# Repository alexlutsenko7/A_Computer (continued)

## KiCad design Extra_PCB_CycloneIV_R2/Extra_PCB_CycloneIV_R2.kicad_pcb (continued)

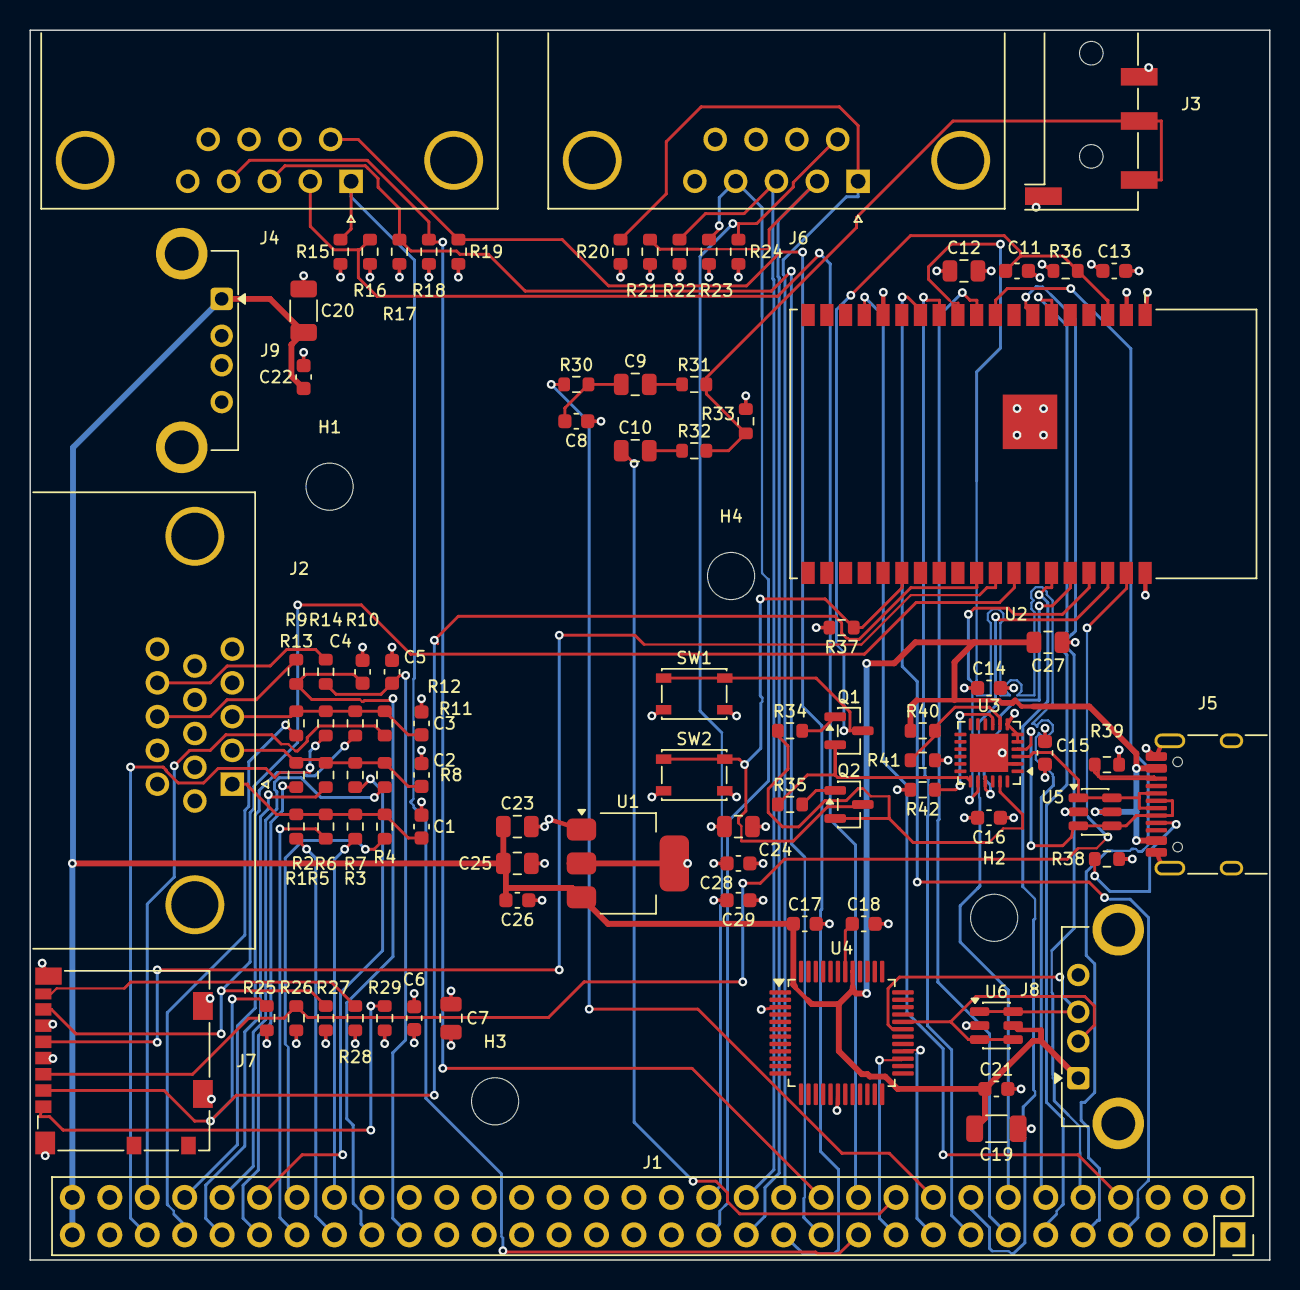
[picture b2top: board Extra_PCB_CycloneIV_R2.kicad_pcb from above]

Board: 4 copper layers, 84.1 x 83.4 mm, 94 parts (0 on the bottom side), 73 nets.

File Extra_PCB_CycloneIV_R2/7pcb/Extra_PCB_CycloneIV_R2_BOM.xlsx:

Item | Qty | Designator | Value | Description | Manufacturer | Manufacturer Part # | Footprint | Mount | LCSC Part #
1 | 5 | C1, C2, C3, C4, C5 | 6p8 | Capacitor 6.8 pF C0G / NP0 0603, 50 V | any |  | C_0603_1608Metric | SMD | C318672
2 | 11 | C6, C8, C13, C15, C16, C17, C21, C22, C26, C28, C29 | 0.1u | Capacitor 100 nF X7R 0603, 16 V or more | any |  | C_0603_1608Metric | SMD | C14663
3 | 7 | C7, C9, C10, C23, C24, C25, C27 | 10u | Capacitor 10 uF X5R 0805, 25 V | Samsung | CL21A106KAYNNNE | C_0805_2012Metric | SMD | C15850
4 | 2 | C11, C14 | 1u | Capacitor 1 uF X5R 0603, 50 V | Samsung | CL10A105KB8NNNC | C_0603_1608Metric | SMD | C15849
5 | 1 | C12 | 22u | Capacitor 22 uF X5R 0805, 25 V | Samsung | CL21A226MAQNNNE | C_0805_2012Metric | SMD | C45783
6 | 1 | C18 | 4.7u | Capacitor 4.7 uF X5R 0603, 16 V | Samsung | CL10A475KO8NNNC | C_0603_1608Metric | SMD | C19666
7 | 2 | C19, C20 | 100u | Capacitor 100 uF X5R 1206, 6.3 V | Samsung | CL31A107MQHNNNE | C_1206_3216Metric | SMD | C15008
8 | 1 | J2 | VGA | D-sub HD 15 socket (VGA), right angle, through hole | CONNFLY | DS1038 series | DSUB-15-HD_Socket_Horizontal_P2.29x2.54mm_CONNFLY_DS1038 | THT | C75754
9 | 1 | J3 | Audio out | 3.5 mm audio jack, 4 pole, SMD | Korean Hroparts | PJ-320D-4A | Jack_3.5mm_KoreanHropartsElec_PJ-320D-4A_Horizontal | SMD | C95562
10 | 2 | J4, J6 | Joystick 2 / Joystick 1 | D-sub 9 plug (pins), right angle, through hole | CONNFLY | DS1037 series | DSUB-9_Pins_Horizontal_P2.77x2.84mm_EdgePinOffset7.70mm_Housed_MountingHolesOff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 | THT | C75750
11 | 1 | J5 | USB-C 5V / console | USB Type-C receptacle, 16 pin, SMD | Korean Hroparts | TYPE-C-31-M-12 | USB_C_Receptacle_HRO_TYPE-C-31-M-12 | SMD | C165948
12 | 1 | J7 | microSD | microSD card socket, push-push | Molex | 104031-0811 | microSD_HC_Molex_104031-0811 | SMD | C585350
13 | 2 | J8, J9 | USB 5V (HDMI dongle) / USB keyboard | USB Type-A receptacle, right angle, through hole | CONNFLY | DS1095-WNR0 | USB_A_Connfly_DS1095 | THT | C19944603
14 | 2 | Q1, Q2 | MMBT3904 | NPN transistor SOT-23 | JSCJ (or any) | MMBT3904 | SOT-23 | SMD | C20526
15 | 3 | R1, R5, R9 | 523 | Resistor 523 R 1 % 0603 | any |  | R_0603_1608Metric | SMD | C23199
16 | 3 | R2, R6, R10 | 1.05k | Resistor 1.05 k 1 % 0603 | any |  | R_0603_1608Metric | SMD | C22832
17 | 3 | R3, R7, R11 | 2.1k | Resistor 2.1 k 1 % 0603 | any |  | R_0603_1608Metric | SMD | C22902
18 | 3 | R4, R8, R12 | 4.22k | Resistor 4.22 k 1 % 0603 | any |  | R_0603_1608Metric | SMD | C23042
19 | 2 | R13, R14 | 22 | Resistor 22 R 1 % 0603 | any |  | R_0603_1608Metric | SMD | C23345
20 | 10 | R15, R16, R17, R18, R19, R20, R21, R22, R23, R24 | 3k3 | Resistor 3.3 k 1 % 0603 | any |  | R_0603_1608Metric | SMD | C22978
21 | 9 | R25, R26, R27, R28, R29, R34, R35, R36, R37 | 10k | Resistor 10 k 1 % 0603 | any |  | R_0603_1608Metric | SMD | C25804
22 | 1 | R30 | 68 | Resistor 68 R 1 % 0603 | any |  | R_0603_1608Metric | SMD | C27592
23 | 2 | R31, R32 | 2.2k | Resistor 2.2 k 1 % 0603 | any |  | R_0603_1608Metric | SMD | C4190
24 | 2 | R33, R42 | 1k | Resistor 1 k 1 % 0603 | any |  | R_0603_1608Metric | SMD | C21190
25 | 2 | R38, R39 | 5.1k | Resistor 5.1 k 1 % 0603 | UNI-ROYAL (or any) | 0603WAF5101T5E | R_0603_1608Metric | SMD | C23186
26 | 1 | R40 | 22k | Resistor 22 k 1 % 0603 | UNI-ROYAL (or any) | 0603WAF2202T5E | R_0603_1608Metric | SMD | C31850
27 | 1 | R41 | 47.5k | Resistor 47.5 k 1 % 0603 | any |  | R_0603_1608Metric | SMD | C23061
28 | 2 | SW1, SW2 | BOOT / EN | Tactile switch SMD | C&K | PTS810 series | SW_SPST_PTS810 | SMD | C116501
29 | 1 | U1 | LDL1117S33R | LDO regulator 3.3 V 1.2 A, SOT-223 | STMicroelectronics | LDL1117S33R | SOT-223-3_TabPin2 | SMD | C435835
30 | 1 | U2 | ESP32-WROVER-E-N16R8 | Wi-Fi / Bluetooth module, 16 MB flash, 8 MB PSRAM | Espressif | ESP32-WROVER-E-N16R8 | ESP32-WROVER-E | SMD | C529589
31 | 1 | U3 | CP2102N-A02-GQFN24 | USB to UART bridge, QFN-24 | Silicon Labs | CP2102N-A02-GQFN24 | QFN-24-1EP_4x4mm_P0.5mm_EP2.6x2.6mm | SMD | C969151
32 | 1 | U4 | CH9350L | USB keyboard / mouse to UART, LQFP-48 | WCH | CH9350L | LQFP-48_7x7mm_P0.5mm | SMD | C109472
33 | 2 | U5, U6 | USBLC6-2SC6 | USB ESD protection, SOT-23-6 | STMicroelectronics | USBLC6-2SC6 | SOT-23-6 | SMD | C7519

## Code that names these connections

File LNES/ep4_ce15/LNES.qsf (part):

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
# Extra_PCB_CycloneIV I/O board: its J1 is wired to U8 with each pin pair swapped
# (J1 pin 2k-1 -> U8 pin 2k, J1 pin 2k -> U8 pin 2k-1). Comment: I/O board J1 pin / U8 pin.
set_location_assignment PIN_AB13 -to ESP_SCK        # J1.7 / U8.8
set_location_assignment PIN_AA13 -to ESP_MOSI       # J1.8 / U8.7
set_location_assignment PIN_AB14 -to ESP_CS_N       # J1.9 / U8.10
set_location_assignment PIN_AA14 -to ESP_MISO       # J1.10 / U8.9
set_location_assignment PIN_AB15 -to ESP_IRQ        # J1.11 / U8.12
set_location_assignment PIN_AA15 -to BT_BCLK        # J1.12 / U8.11
set_location_assignment PIN_AB16 -to BT_LRCK        # J1.13 / U8.14
set_location_assignment PIN_AA16 -to BT_DATA        # J1.14 / U8.13
set_location_assignment PIN_AB17 -to BT_TX          # J1.15 / U8.16
set_location_assignment PIN_AA17 -to BT_RX          # J1.16 / U8.15
set_location_assignment PIN_AB18 -to KB_IN          # J1.17 / U8.18
set_location_assignment PIN_AA18 -to AUDIO_AY       # J1.18 / U8.17
set_location_assignment PIN_AB19 -to KB_OUT         # J1.19 / U8.20
set_location_assignment PIN_AA19 -to AUDIO_BEEP     # J1.20 / U8.19
set_location_assignment PIN_AB20 -to JOY1_UP_N      # J1.21 / U8.22
set_location_assignment PIN_AA20 -to JOY1_DOWN_N    # J1.22 / U8.21
set_location_assignment PIN_Y21 -to JOY1_LEFT_N    # J1.23 / U8.24
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set_location_assignment PIN_V22 -to JOY2_LEFT_N    # J1.28 / U8.27
set_location_assignment PIN_U21 -to JOY2_RIGHT_N   # J1.29 / U8.30
set_location_assignment PIN_U22 -to JOY2_FIRE_N    # J1.30 / U8.29
set_location_assignment PIN_H21 -to VGA_VS         # J1.45 / U8.46
set_location_assignment PIN_F21 -to VGA_HS         # J1.47 / U8.48
# sync pins at the weakest drive (3.3-V LVCMOS, 2 mA: slower edges): the HSYNC edge coupled onto the colour lines (~30 mV spike 40 pixels after the
# active area), and monitors auto-adjusted to it as the picture edge (a line at the right)
set_instance_assignment -name CURRENT_STRENGTH_NEW 2MA -to VGA_HS
set_instance_assignment -name CURRENT_STRENGTH_NEW 2MA -to VGA_VS
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
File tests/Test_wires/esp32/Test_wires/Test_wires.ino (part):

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
// FPGA -> ESP32; the FPGA marks frames on these with id C1..C4 (in this order)
static const Wire RET[4] = {
    {35, "GPIO35 (D35)", "R1", "U7.7",  "ESP_MISO"},
    {34, "GPIO34 (D34)", "R2", "U7.8",  "ESP_IRQ"},
    {22, "GPIO22 (D22)", "F1", "U7.19", "BT_DATA"},
    {16, "GPIO16 (RX2)", "F2", "U7.20", "BT_TX"},
};
// ESP32 -> FPGA; bit n of the FPGA's level byte / counter n
static const Wire FWD[6] = {
    {14, "GPIO14 (D14)", "P1", "U7.9",  "ESP_SCK"},
    {13, "GPIO13 (D13)", "P2", "U7.10", "ESP_MOSI"},
    {33, "GPIO33 (D33)", "N1", "U7.11", "ESP_CS_N"},
    {26, "GPIO26 (D26)", "H1", "U7.17", "BT_BCLK"},
    {25, "GPIO25 (D25)", "H2", "U7.18", "BT_LRCK"},
    {17, "GPIO17 (TX2)", "E1", "U7.21", "BT_RX"},
};
static const int SD_SCK = 18, SD_MISO = 19, SD_MOSI = 23, SD_CS = 5;

SPIClass sdspi(VSPI);
SPIClass fastspi(HSPI);
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    for (uint32_t f : hz) {
        sdspi.end();
        sdspi.begin(SD_SCK, SD_MISO, SD_MOSI, SD_CS);
        gpio_pullup_en((gpio_num_t)SD_MISO);        // internal pull-up on MISO (an external 10k-47k is better)
        if (SD.begin(SD_CS, sdspi, f)) {
            sd_mounted = true;
            const char *t = SD.cardType() == CARD_MMC ? "MMC" : SD.cardType() == CARD_SD ? "SDSC"
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    SD.end();
    sdspi.end();
    sd_mounted = false;
    const int P[4] = {SD_CS, SD_SCK, SD_MOSI, SD_MISO};
    Serial.println("SD probe: CMD0 at ~100 kHz with every assignment of GPIO5/18/23/19 (expect answer 01)");
    int found = 0;
    int idx[4] = {0, 1, 2, 3};
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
